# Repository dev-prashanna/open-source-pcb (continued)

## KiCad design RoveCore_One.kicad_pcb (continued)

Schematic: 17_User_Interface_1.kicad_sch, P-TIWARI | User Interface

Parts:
BZ1: PKLCS1212E4001-R1; Buzzer_Murata_PKLCS1212E; MPN PKLCS1212E4001-R1
C68: 100nF 16V; C_0603_1608Metric; MPN GRM188R71C104KA01D
D4, D6: GREEN; LED_0603_1608Metric; MPN LTST-C190KGKT
D5: RED; LED_0603_1608Metric; MPN LTST-C190KRKT
D7: BLUE; LED_0603_1608Metric; MPN LTST-C193TBKT-5A
D8: SS34; D_SMA; MPN SS34
Q6, Q7: AO3400A; SOT-23; MPN AO3400A
R62: 10k; R_0603_1608Metric; MPN RC0603FR-0710KL
R63, R64, R65, R66, R69: 1k; R_0603_1608Metric; MPN RC0603FR-071KL
R67, R70: 100; R_0603_1608Metric; MPN RC0603FR-07100RL
R68, R71: 100k; R_0603_1608Metric; MPN RC0603FR-07100KL
SW3: SW3; SW_Push_1P1T-SH_NO_CK_KMR2xxG; MPN KMR221GLFS

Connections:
+3V3: BZ1.1 (+), R62.1, R63.1, R64.1, R65.1, R66.1, R69.1; also elsewhere on the board
BAT5: D8.1 (K); also elsewhere on the board
BUZZ_GATE: Q6.1 (G), R67.2, R68.1
BUZZ_LOW: BZ1.2 (-), Q6.3 (D), R69.2
BUZZ_PWM: R67.1; also elsewhere on the board
EXP_B7: R70.1; also elsewhere on the board
GND: C68.2, D4.1 (K), Q6.2 (S), Q7.2 (S), R68.2, R71.2, SW3.2; also elsewhere on the board
LED_B: D7.2 (A), R66.2
LED_G: D6.2 (A), R65.2
LED_R: D5.2 (A), R64.2
LOAD_GATE: Q7.1 (G), R70.2, R71.1
LOAD_LOW: D8.2 (A), Q7.3 (D); also elsewhere on the board
POWER_LED: D4.2 (A), R63.2
RGB_B: D7.1 (K); also elsewhere on the board
RGB_G: D6.1 (K); also elsewhere on the board
RGB_R: D5.1 (K); also elsewhere on the board
USER_BTN: C68.1, R62.2, SW3.1; also elsewhere on the board

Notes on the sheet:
R/G/B discrete programmable LEDs on expander GPA5..7; use green for Wi-Fi status. Piezo buzzer via GPIO2 MOSFET and discharge resistor. User button active LOW on GPA4. GPB7 load output 5V/250mA max, diode-protected for small inductive loads. BAT5 accessory budget shared. CAN: external 3V3 transceiv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

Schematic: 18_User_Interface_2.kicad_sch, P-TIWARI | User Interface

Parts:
J23: LOAD 5V 0.25A; JST_GH_SM02B-GHS-TB_1x02-1MP_P1.25mm_Horizontal; MPN SM02B-GHS-TB(LF)(SN)

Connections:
BAT5: J23.1; also elsewhere on the board
LOAD_LOW: J23.2; also elsewhere on the board

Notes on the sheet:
R/G/B discrete programmable LEDs on expander GPA5..7; use green for Wi-Fi status. Piezo buzzer via GPIO2 MOSFET and discharge resistor. User button active LOW on GPA4. GPB7 load output 5V/250mA max, diode-protected for small inductive loads. BAT5 accessory budget shared. CAN: external 3V3 transceiv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

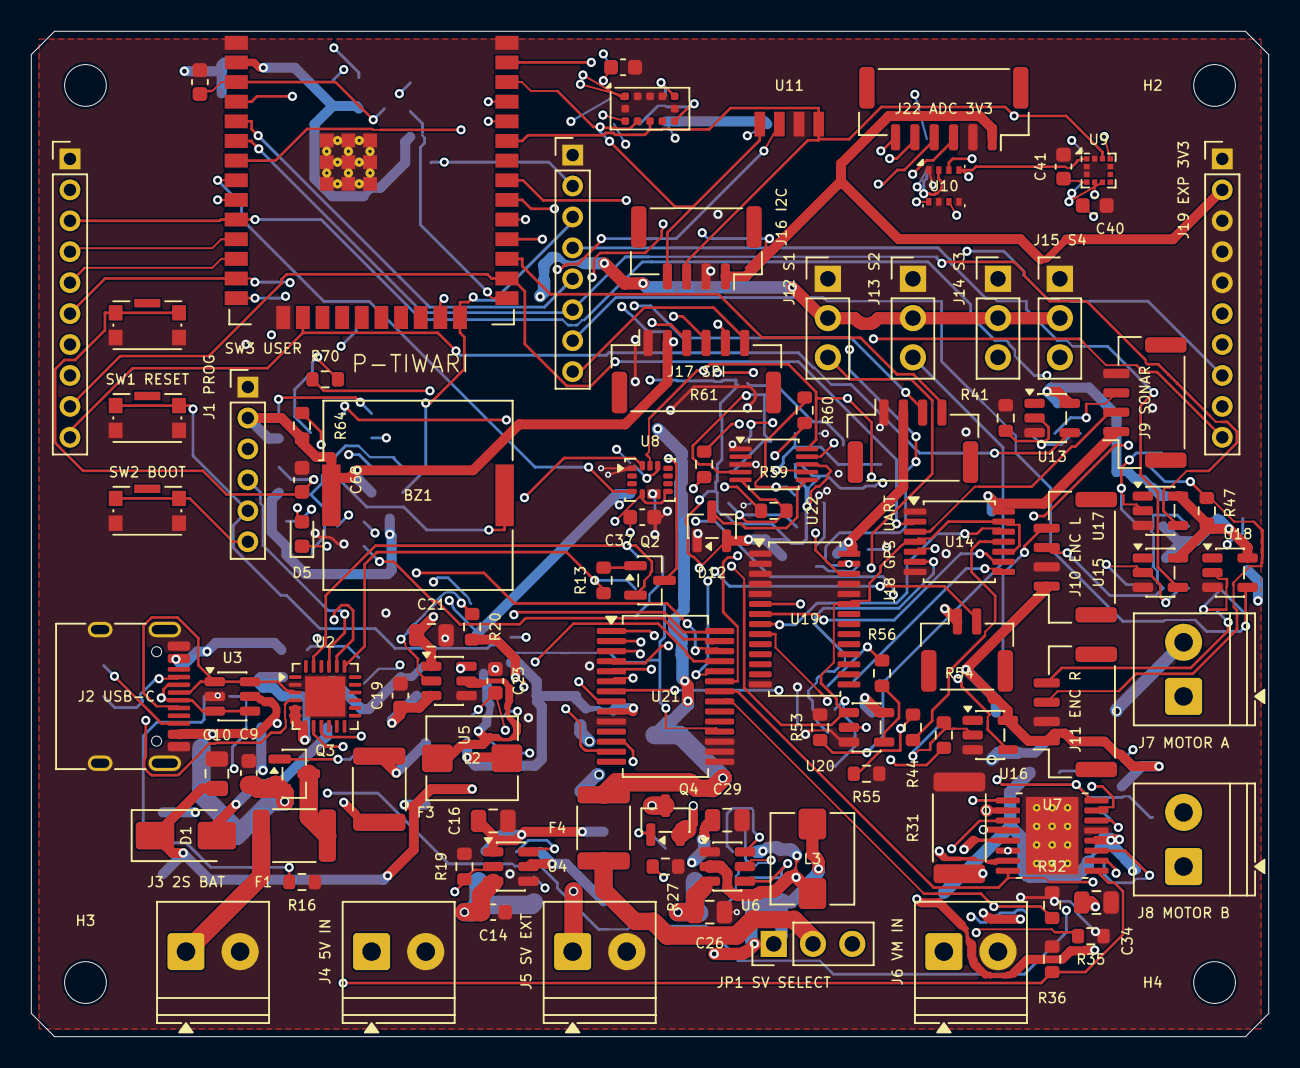
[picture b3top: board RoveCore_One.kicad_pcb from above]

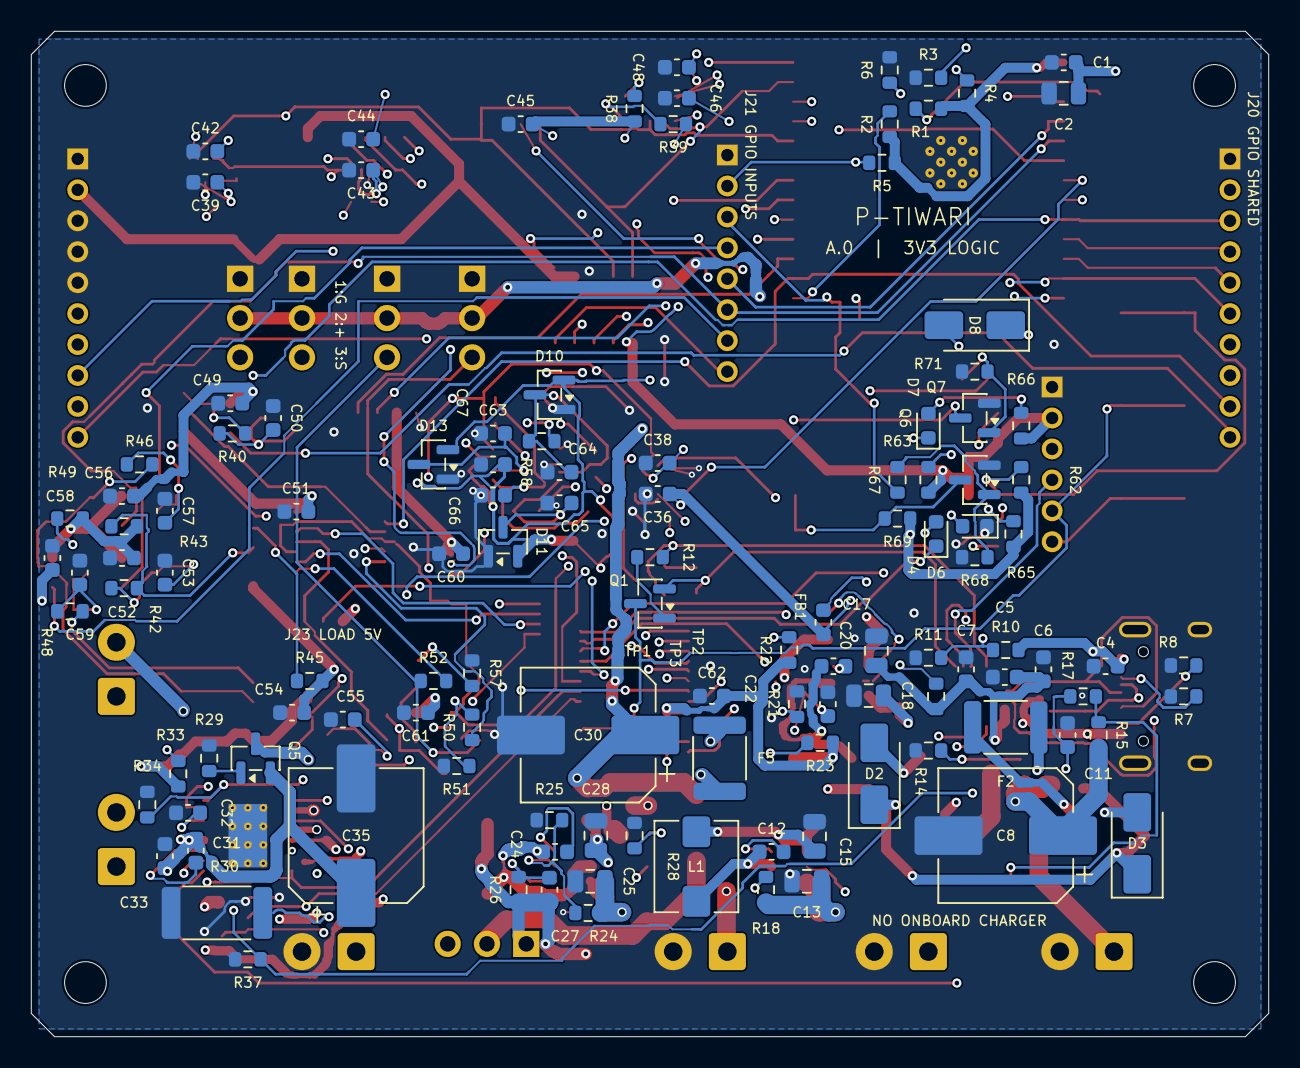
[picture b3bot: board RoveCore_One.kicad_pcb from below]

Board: 4 copper layers, 80.0 x 65.0 mm, 224 parts (122 on the bottom side), 135 nets.

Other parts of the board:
H1, H2, H3, H4: MountingHole_2.7mm_M2.5

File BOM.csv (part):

Reference,Value,MPN,Manufacturer,Footprint,Section,Datasheet
U1,ESP32-WROOM-32E-N8,ESP32-WROOM-32E-N8,Espressif,RoveCore:ESP32-WROOM-32E_Board,Controller,https://documentation.espressif.com/esp32-wroom-32e_esp32-wr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
C1,100nF 16V,GRM188R71C104KA01D,Murata,Capacitor_SMD:C_0603_1608Metric,Controller,
C2,22uF 10V,GRM21BR61A226ME44L,Murata,Capacitor_SMD:C_0805_2012Metric,Controller,
R1,10k,RC0603FR-0710KL,Yageo,Resistor_SMD:R_0603_1608Metric,Controller,
C3,1uF 16V,GRM188R61C105KA12D,Murata,Capacitor_SMD:C_0603_1608Metric,Controller,
R2,10k,RC0603FR-0710KL,Yageo,Resistor_SMD:R_0603_1608Metric,Controller,
R3,10k,RC0603FR-0710KL,Yageo,Resistor_SMD:R_0603_1608Metric,Controller,
R4,10k,RC0603FR-0710KL,Yageo,Resistor_SMD:R_0603_1608Metric,Controller,
R5,10k,RC0603FR-0710KL,Yageo,Resistor_SMD:R_0603_1608Metric,Controller,
R6,100k,RC0603FR-07100KL,Yageo,Resistor_SMD:R_0603_1608Metric,Controller,
SW1,SW1,KMR221GLFS,C&K,Button_Switch_SMD:SW_Push_1P1T-SH_NO_CK_KMR2xxG,Controller,
SW2,SW2,KMR221GLFS,C&K,Button_Switch_SMD:SW_Push_1P1T-SH_NO_CK_KMR2xxG,Controller,
J1,SERVICE 3V3,M22-2010605,Harwin,Connector_PinHeader_2.00mm:PinHeader_1x06_P2.00mm_Vertical,Controller,
J2,USB-C 5V DATA,TYPE-C-31-M-12,HRO,Connector_USB:USB_C_Receptacle_HRO_TYPE-C-31-M-12,USB Programming,
R7,5.1k,RC0603FR-075K1L,Yageo,Resistor_SMD:R_0603_1608Metric,USB Programming,
R8,5.1k,RC0603FR-075K1L,Yageo,Resistor_SMD:R_0603_1608Metric,USB Programming,
C4,1uF 16V,GRM188R61C105KA12D,Murata,Capacitor_SMD:C_0603_1608Metric,USB Programming,
U2,CP2102N-A02-GQFN24,CP2102N-A02-GQFN24,Silicon Labs,Package_DFN_QFN:QFN-24-1EP_4x4mm_P0.5mm_EP2.6x2.6mm,USB Programming,https://www.silabs.com/documents/public/data-sheets/cp2102n-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
C5,100nF 16V,GRM188R71C104KA01D,Murata,Capacitor_SMD:C_0603_1608Metric,USB Programming,
C6,100nF 16V,GRM188R71C104KA01D,Murata,Capacitor_SMD:C_0603_1608Metric,USB Programming,
C7,4.7uF 10V,GRM188R61A475KE15D,Murata,Capacitor_SMD:C_0603_1608Metric,USB Programming,
R9,1k,RC0603FR-071KL,Yageo,Resistor_SMD:R_0603_1608Metric,USB Programming,
R10,22.1k,RC0603FR-0722K1L,Yageo,Resistor_SMD:R_0603_1608Metric,USB Programming,
R11,47.5k,RC0603FR-0747K5L,Yageo,Resistor_SMD:R_0603_1608Metric,USB Programming,
U3,USBLC6-2SC6,USBLC6-2SC6,STMicroelectronics,Package_TO_SOT_SMD:SOT-23-6,USB Programming,
Q1,MMBT3904,MMBT3904,onsemi,Package_TO_SOT_SMD:SOT-23,USB Programming,
R12,10k,RC0603FR-0710KL,Yageo,Resistor_SMD:R_0603_1608Metric,USB Programming,
Q2,MMBT3904,MMBT3904,onsemi,Package_TO_SOT_SMD:SOT-23,USB Programming,
R13,10k,RC0603FR-0710KL,Yageo,Resistor_SMD:R_0603_1608Metric,USB Programming,
J3,2S BAT 6.4-8.4V,1984617,Phoenix Contact,"TerminalBlock_Phoenix:TerminalBlock_Phoenix_PT-1,5-2-3.5-H_1x02_P3.50mm_Horizontal",Power Inputs,
F1,2A hold,1812L200/16DR,Littelfuse,Fuse:Fuse_1812_4532Metric,Power Inputs,
Q3,AO3401A,AO3401A,Alpha & Omega Semiconductor,Package_TO_SOT_SMD:SOT-23,Power Inputs,https://www.aosmd.com/sites/default/files/res/datasheets/AO3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
R14,100k,RC0603FR-07100KL,Yageo,Resistor_SMD:R_0603_1608Metric,Power Inputs,
C8,470uF 16V,EEE-FK1C471P,Panasonic,Capacitor_SMD:CP_Elec_8x10.5,Power Inputs,
C9,100nF 16V,GRM188R71C104KA01D,Murata,Capacitor_SMD:C_0603_1608Metric,Power Inputs,
J4,EXT 5V LOGIC,1984617,Phoenix Contact,"TerminalBlock_Phoenix:TerminalBlock_Phoenix_PT-1,5-2-3.5-H_1x02_P3.50mm_Horizontal",Power Inputs,
F2,1.1A hold,1812L110/16DR,Littelfuse,Fuse:Fuse_1812_4532Metric,Power Inputs,
F3,0.5A hold,1812L050/24DR,Littelfuse,Fuse:Fuse_1812_4532Metric,Power Inputs,
D1,SS34,SS34,Diodes Inc.,Diode_SMD:D_SMA,Power Inputs,
D2,SS34,SS34,Diodes Inc.,Diode_SMD:D_SMA,Power Inputs,
D3,SS34,SS34,Diodes Inc.,Diode_SMD:D_SMA,Power Inputs,
C10,22uF 10V,GRM21BR61A226ME44L,Murata,Capacitor_SMD:C_0805_2012Metric,Power Inputs,
R15,100k,RC0603FR-07100KL,Yageo,Resistor_SMD:R_0603_1608Metric,Power Inputs,
R16,33k,RC0603FR-0733KL,Yageo,Resistor_SMD:R_0603_1608Metric,Power Inputs,
R17,1k,RC0603FR-071KL,Yageo,Resistor_SMD:R_0603_1608Metric,Power Inputs,
C11,100nF 16V,GRM188R71C104KA01D,Murata,Capacitor_SMD:C_0603_1608Metric,Power Inputs,
U4,AP63205WU-7,AP63205WU-7,Diodes Inc.,Package_TO_SOT_SMD:TSOT-23-6,Logic Regulators,https://www.diodes.com/datasheet/download/AP63200-AP63201-AP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
R18,100k,RC0603FR-07100KL,Yageo,Resistor_SMD:R_0603_1608Metric,Logic Regulators,
R19,27.4k,RC0603FR-0727K4L,Yageo,Resistor_SMD:R_0603_1608Metric,Logic Regulators,
C12,100nF 16V,GRM188R71C104KA01D,Murata,Capacitor_SMD:C_0603_1608Metric,Logic Regulators,
C13,10uF 16V,GRM21BR61C106KE15L,Murata,Capacitor_SMD:C_0805_2012Metric,Logic Regulators,
C14,100nF 16V,GRM188R71C104KA01D,Murata,Capacitor_SMD:C_0603_1608Metric,Logic Regulators,
L1,4.7uH,SRP5030T-4R7M,Bourns,Inductor_SMD:L_Bourns_SRP5030T,Logic Regulators,
C15,22uF 10V,GRM21BR61A226ME44L,Murata,Capacitor_SMD:C_0805_2012Metric,Logic Regulators,
C16,22uF 10V,GRM21BR61A226ME44L,Murata,Capacitor_SMD:C_0805_2012Metric,Logic Regulators,
U5,AP63203WU-7,AP63203WU-7,Diodes Inc.,Package_TO_SOT_SMD:TSOT-23-6,Logic Regulators,https://www.diodes.com/datasheet/download/AP63200-AP63201-AP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
R20,100k,RC0603FR-07100KL,Yageo,Resistor_SMD:R_0603_1608Metric,Logic Regulators,
R21,100k,RC0603FR-07100KL,Yageo,Resistor_SMD:R_0603_1608Metric,Logic Regulators,
C17,100nF 16V,GRM188R71C104KA01D,Murata,Capacitor_SMD:C_0603_1608Metric,Logic Regulators,
C18,10uF 16V,GRM21BR61C106KE15L,Murata,Capacitor_SMD:C_0805_2012Metric,Logic Regulators,
C19,100nF 16V,GRM188R71C104KA01D,Murata,Capacitor_SMD:C_0603_1608Metric,Logic Regulators,
L2,4.7uH,SRP5030T-4R7M,Bourns,Inductor_SMD:L_Bourns_SRP5030T,Logic Regulators,
C20,22uF 10V,GRM21BR61A226ME44L,Murata,Capacitor_SMD:C_0805_2012Metric,Logic Regulators,
C21,22uF 10V,GRM21BR61A226ME44L,Murata,Capacitor_SMD:C_0805_2012Metric,Logic Regulators,
FB1,600R @100MHz,BLM18AG601SN1D,Murata,Inductor_SMD:L_0603_1608Metric,Logic Regulators,
C22,4.7uF 10V,GRM188R61A475KE15D,Murata,Capacitor_SMD:C_0603_1608Metric,Logic Regulators,
C23,100nF 16V,GRM188R71C104KA01D,Murata,Capacitor_SMD:C_0603_1608Metric,Logic Regulators,
R22,2.2k,RC0603FR-072K2L,Yageo,Resistor_SMD:R_0603_1608Metric,Logic Regulators,
R23,2.2k,RC0603FR-072K2L,Yageo,Resistor_SMD:R_0603_1608Metric,Logic Regulators,
U6,TPS54302DDCR,TPS54302DDCR,Texas Instruments,Package_TO_SOT_SMD:SOT-23-6,Servo Power,https://www.ti.com/lit/ds/symlink/tps54302.pdf
R24,100k,RC0603FR-07100KL,Yageo,Resistor_SMD:R_0603_1608Metric,Servo Power,
R25,27.4k,RC0603FR-0727K4L,Yageo,Resistor_SMD:R_0603_1608Metric,Servo Power,
C24,100nF 16V,GRM188R71C104KA01D,Murata,Capacitor_SMD:C_0603_1608Metric,Servo Power,
C25,10uF 16V,GRM21BR61C106KE15L,Murata,Capacitor_SMD:C_0805_2012Metric,Servo Power,
C26,10uF 16V,GRM21BR61C106KE15L,Murata,Capacitor_SMD:C_0805_2012Metric,Servo Power,
L3,10uH,SRP5030T-100M,Bourns,Inductor_SMD:L_Bourns_SRP5030T,Servo Power,
R26,100k,RC0603FR-07100KL,Yageo,Resistor_SMD:R_0603_1608Metric,Servo Power,
R27,13.3k,RC0603FR-0713K3L,Yageo,Resistor_SMD:R_0603_1608Metric,Servo Power,
C27,75pF 50V,GRM1885C1H750JA01D,Murata,Capacitor_SMD:C_0603_1608Metric,Servo Power,
C28,22uF 10V,GRM21BR61A226ME44L,Murata,Capacitor_SMD:C_0805_2012Metric,Servo Power,
C29,22uF 10V,GRM21BR61A226ME44L,Murata,Capacitor_SMD:C_0805_2012Metric,Servo Power,
J5,SERVO EXT 5-6V,1984617,Phoenix Contact,"TerminalBlock_Phoenix:TerminalBlock_Phoenix_PT-1,5-2-3.5-H_1x02_P3.50mm_Horizontal",Servo Power,
Q4,AO3401A,AO3401A,Alpha & Omega Semiconductor,Package_TO_SOT_SMD:SOT-23,Servo Power,https://www.aosmd.com/sites/default/files/res/datasheets/AO3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
R28,100k,RC0603FR-07100KL,Yageo,Resistor_SMD:R_0603_1608Metric,Servo Power,
JP1,SERVO SELECT 1-2 BAT / 2-3 EXT,61300311121,Wurth Elektronik,Connector_PinHeader_2.54mm:PinHeader_1x03_P2.54mm_Vertical,Servo Power,
F4,2A hold,1812L200/16DR,Littelfuse,Fuse:Fuse_1812_4532Metric,Servo Power,
C30,470uF 16V,EEE-FK1C471P,Panasonic,Capacitor_SMD:CP_Elec_8x10.5,Servo Power,
J6,VM 3-8.4V,1984617,Phoenix Contact,"TerminalBlock_Phoenix:TerminalBlock_Phoenix_PT-1,5-2-3.5-H_1x02_P3.50mm_Horizontal",Motor Driver,
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
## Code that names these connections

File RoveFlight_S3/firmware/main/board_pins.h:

// Generated from verified GPIO_Allocation.csv. RF-S3-A0 / N8R2 only.
#pragma once
#define PIN_BOOT 0
#define PIN_CURRENT_ADC 1
#define PIN_BAT_ADC 2
#define PIN_PWM_M1 4
#define PIN_PWM_M2 5
#define PIN_PWM_M3 6
#define PIN_PWM_M4 7
#define PIN_I2C_SDA 8
#define PIN_IMU_INT 9
#define PIN_IMU_CS 10
#define PIN_SPI_MOSI 11
#define PIN_SPI_SCK 12
#define PIN_SPI_MISO 13
#define PIN_BARO_CS 14
#define PIN_IR_RX 15
#define PIN_TOF_INT 16
#define PIN_TOF_XSHUT 17
#define PIN_I2C_SCL 18
#define PIN_USB_DM 19
#define PIN_USB_DP 20
#define PIN_STATUS_LED 21
#define PIN_ARM_CLK 38
#define PIN_WD_HEARTBEAT 39
#define PIN_KILL_OD 40
#define PIN_RC_RX 41
#define PIN_RC_TX 42
#define PIN_DEBUG_TX 43
#define PIN_DEBUG_RX 44
#define PIN_FLOW_CS 47
#define PIN_FLOW_INT 48

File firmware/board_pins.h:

// P-TIWARI A.0; pin contract only, not validated application firmware.
#pragma once
namespace p_tiwari {
constexpr int PIN_BOOT = 0;
constexpr int PIN_U0_TX = 1;
constexpr int PIN_BUZZ_PWM = 2;
constexpr int PIN_U0_RX = 3;
constexpr int PIN_US_TRIG = 4;
constexpr int PIN_SPI_CS = 5;
constexpr int PIN_STRAP12 = 12;
constexpr int PIN_US_ECHO = 13;
constexpr int PIN_M_B2 = 14;
constexpr int PIN_SERVO_OE = 15;
constexpr int PIN_UART_RX = 16;
constexpr int PIN_UART_TX = 17;
constexpr int PIN_SPI_SCK = 18;
constexpr int PIN_SPI_MISO = 19;
constexpr int PIN_I2C_SDA = 21;
constexpr int PIN_I2C_SCL = 22;
constexpr int PIN_SPI_MOSI = 23;
constexpr int PIN_M_A1 = 25;
constexpr int PIN_M_A2 = 26;
constexpr int PIN_M_B1 = 27;
constexpr int PIN_IMU_INT = 32;
constexpr int PIN_BAT_ADC = 33;
constexpr int PIN_ENC_RA = 34;
constexpr int PIN_ENC_RB = 35;
constexpr int PIN_ENC_LA = 36;
constexpr int PIN_ENC_LB = 39;
constexpr unsigned IMU_ADDR=0x6A, MAG_ADDR=0x1C, BME_ADDR=0x76, ALS_ADDR=0x10;
constexpr unsigned TOF_ADDR=0x29, PWM_ADDR=0x40, EXP_ADDR=0x20, ADC_ADDR=0x48;
}

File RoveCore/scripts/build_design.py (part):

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
d.section='Encoder Interfaces'
for idx,xy,labels,raws in [(0,(72,33),['ENC_LA','ENC_LB'],['ENC_LA_RAW','ENC_LB_RAW']),(1,(72,38),['ENC_RA','ENC_RB'],['ENC_RA_RAW','ENC_RB_RAW'])]:
 d.conn('J'+str(10+idx),['+3V3','GND',*raws],'ENC '+('LEFT' if idx==0 else 'RIGHT'),xy,'gh',90)
 for j,(net,raw) in enumerate(zip(labels,raws)):
  ref='U'+str(15+idx*2+j)
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for ref,net,xy in [('TP1','EXP_B0',(40.2806,39.0703)),('TP2','EXP_B1',(39.4113,39.4811)),('TP3','EXP_B2',(39.377,40.2551))]:
 d.add('Connector','TestPoint',net,{'1':net},'RoveCore:ServicePad_0.5mm',xy,ref=ref,mpn='PCB copper feature',mfr='PCB fabricator',side='B')
# Shared test/header access to every practical controller pin; GPIO12 is reserved.
d.conn('J20',['GND','+3V3','M_A1','M_A2','M_B1','M_B2','IMU_INT','BAT_ADC','US_TRIG','US_ECHO'],'ESP GPIO SHARED',(6,7),'header')
d.conn('J21',['GND','SERVO_OE','BUZZ_PWM','ENC_LA','ENC_LB','ENC_RA','ENC_RB','SPI_CS'],'ESP GPIO INPUTS',(35,8),'header')
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
d.section='Analog Expansion'
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
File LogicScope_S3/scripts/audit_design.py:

"""Independent manifest/XML/PCB pin checks and ground-return geometry audit."""
from route_utils import *
import xml.etree.ElementTree as ET
from collections import defaultdict
from shapely.ops import unary_union
parts=json.loads((ROOT/'design.json').read_text());manifest={(c['ref'],pin):net for c in parts for pin,net in c['nets'].items()};xml=ET.parse(ROOT/'reports/LogicScope_S3.xml').getroot();actual={}
for net in xml.find('nets'):
 for q in net.findall('node'):actual[(q.attrib['ref'],q.attrib['pin'])]=net.attrib['name'].lstrip('/')
errors=[]
for (ref,num),net in manifest.items():
 pads=[q for q in fps[ref].Pads() if q.GetNumber()==num]
 if not pads:errors.append([ref,num,'missing pad'])
 for q in pads:
  if net is None:
   if q.GetNetname() and not q.GetNetname().startswith('unconnected-'):errors.append([ref,num,'unexpected connected NC',q.GetNetname()])
  elif actual.get((ref,num))!=net or q.GetNetname()!=net:errors.append([ref,num,net,actual.get((ref,num)),q.GetNetname()])
for key,net in actual.items():
 if not key[0].startswith('#') and key not in manifest and not net.startswith('unconnected-'):errors.append(['unexpected pin',key,net])
def nn(ref,num):return actual.get((ref,str(num)))
checks={
 'manifest_schematic_and_pcb_match':not errors,
 'eight_parallel_bits':all(nn('U1',4+i)==nn('U2',18-i)==f'D{i}' for i in range(8)),
 'input_protection_each_channel':all(nn('R'+str(10+i),1)==f'CH{i}' and nn('R'+str(10+i),2)==nn('U2',2+i)==f'IN{i}' for i in range(8)),
 'pulldowns_each_input':all(nn('R'+str(20+i),1)==f'IN{i}' and nn('R'+str(20+i),2)=='GND' for i in range(8)),
 'buffer_direction_and_supply':nn('U2',1)==nn('U2',20)=='+3V3' and nn('U2',10)=='GND' and nn('U2',19)=='BUF_OE_N',
 'usb_native_gpio19_20':nn('U1',13)=='USB_DM' and nn('U1',14)=='USB_DP',
 'usb_dual_data_pads':nn('J3','A6')==nn('J3','B6')=='USB_DP_CONN' and nn('J3','A7')==nn('J3','B7')=='USB_DM_CONN',
 'usb_cc_separate':nn('J3','A5')==nn('R30',1)=='USB_CC1' and nn('J3','B5')==nn('R31',1)=='USB_CC2' and nn('R30',2)==nn('R31',2)=='GND',
 'buck_pin_map':all(nn('U3',pin)==net for pin,net in [(1,'+3V3'),(2,'VUSB'),(3,'VUSB'),(4,'GND'),(5,'SW'),(6,'BST')]),
 'hardware_clock_loopback':nn('U1',20)==nn('R4',1)=='SAMPLE_CLK' and nn('R4',2)==nn('U1',19)=='CAM_PCLK',
 'no_external_5V_direct_to_mcu':not any(q.GetNetname() in {'USB_5V','VUSB'} or q.GetNetname().startswith('CH') for q in fps['U1'].Pads()),
 'two_copper_layers':b.GetCopperLayerCount()==2,
 'optional_esd_dnp':all(bool(fps[ref].GetAttributes()&p.FP_DNP) for ref in ['U5','U6']),
 'etched_and_silk_tiwari':all(any(isinstance(q,p.PCB_TEXT) and q.GetText()=='TIWARI' and q.GetLayer()==layer for q in b.GetDrawings()) for layer in [p.F_Cu,p.F_SilkS]),
}
for ref,nets in [('J1',['CH0','GND','CH1','GND','CH2','GND','CH3','GND','CH4','GND']),('J2',['CH5','GND','CH6','GND','CH7','GND','VREF_3V3','GND',None,None])]:
 checks[ref+'_pinout']=all(nn(ref,i+1)==net if net else nn(ref,i+1).startswith('unconnected-') for i,net in enumerate(nets))
connectivity={'checks':checks,'errors':errors,'electrical_parts':len(parts),'all_passed':all(checks.values())}
(ROOT/'reports/Connectivity_Audit.json').write_text(json.dumps(connectivity,indent=2)+'\n')

def filled(z):
 ps=z.GetFilledPolysList(z.GetLayer())
 def ring(r):return [(p.ToMM(r.CPoint(k).x),p.ToMM(r.CPoint(k).y)) for k in range(r.PointCount())]
 return [Polygon(ring(ps.COutline(i)),[ring(ps.CHole(i,j)) for j in range(ps.HoleCount(i))]).buffer(0) for i in range(ps.OutlineCount())]
rear_zones=[z for z in b.Zones() if not z.GetIsRuleArea() and z.GetLayer()==p.B_Cu and z.GetNetname()=='GND']
rear_polys=[g for z in rear_zones for g in filled(z)];rear=unary_union(rear_polys)
netstats=defaultdict(lambda:{'length_mm':0.,'rear_length_mm':0.,'vias':0,'widths_mm':set(),'layers':set()});critical_errors=[];plane_gaps=[];via_pad=[]
for tr in b.GetTracks():
 net=tr.GetNetname();e=netstats[net]
 if isinstance(tr,p.PCB_VIA):
  e['vias']+=1;hole=Point(*xy(tr)).buffer(p.ToMM(tr.GetDrill())/2)
  if any(hole.intersects(g) for l in layers for g in smd[l]):via_pad.append({'net':net,'xy':xy(tr)})
  continue
 a,z=tr.GetStart(),tr.GetEnd();path=LineString([(p.ToMM(a.x),p.ToMM(a.y)),(p.ToMM(z.x),p.ToMM(z.y))]);length=p.ToMM(tr.GetLength());e['length_mm']+=length;e['widths_mm'].add(round(p.ToMM(tr.GetWidth()),4));e['layers'].add(b.GetLayerName(tr.GetLayer()))
 if tr.GetLayer()==p.B_Cu:e['rear_length_mm']+=length
 if net in {f'D{i}' for i in range(8)} or net.startswith('USB_D'):
  if tr.GetLayer()!=p.F_Cu:critical_errors.append(net)
  if not rear.buffer(.01).covers(path):plane_gaps.append({'net':net,'length_missing_mm':path.difference(rear.buffer(.01)).length})
for e in netstats.values():
 for key in ['length_mm','rear_length_mm']:e[key]=round(e[key],4)
 for key in ['layers','widths_mm']:e[key]=sorted(e[key])
critical_vias={n:e['vias'] for n,e in netstats.items() if (n.startswith('USB_D') or n in {f'D{i}' for i in range(8)}) and e['vias']}
antenna=[]
for fp in b.GetFootprints():
 for zone in fp.Zones():
  if not zone.GetIsRuleArea():continue
  ps=zone.Outline()
  for i in range(ps.OutlineCount()):
   r=ps.COutline(i);g=Polygon([(p.ToMM(r.CPoint(k).x),p.ToMM(r.CPoint(k).y)) for k in range(r.PointCount())])
   for l in layers:
    if any(g.intersection(s).area>1e-5 for s,n in zip(geoms[l],owners[l]) if n!='__KEEP_OUT'):antenna.append('copper overlap')
   if g.intersection(rear).area>1e-5:antenna.append('rear fill overlap')
physical={'copper_layers':b.GetCopperLayerCount(),'board_mm':[55,40],'nominal_thickness_mm':p.ToMM(b.GetDesignSettings().GetBoardThickness()),'footprints':len(fps),'rear_ground_polygons':len(rear_polys),'rear_ground_area_mm2':round(rear.area,3),'rear_coverage_of_2200mm2_percent':round(100*rear.area/2200,2),'critical_routes_on_wrong_layer':critical_errors,'critical_vias':critical_vias,'critical_centerline_reference_gaps':plane_gaps,'antenna_copper_errors':antenna,'board_via_drills_in_smd_lands':via_pad,'nets':dict(netstats),'performance_validation':'UNMEASURED; finite capture target 1 MS/s, no released continuous rate'}
physical['all_passed']=len(rear_polys)==1 and not any([critical_errors,critical_vias,plane_gaps,antenna,via_pad])
(ROOT/'reports/Physical_Audit.json').write_text(json.dumps(physical,indent=2)+'\n')
with (ROOT/'Placement.csv').open('w') as f:
 w=csv.writer(f);w.writerow(['Reference','Value','X_mm','Y_mm','Rotation_deg','Side','DNP'])
 for ref,fp in sorted(fps.items()):w.writerow([ref,fp.GetValue(),*xy(fp),fp.GetOrientationDegrees(),'F' if fp.GetLayer()==p.F_Cu else 'B','YES' if fp.GetAttributes()&p.FP_DNP else 'NO'])
print('Connectivity checks',checks,'errors',errors)
print('Physical audit:',{k:v for k,v in physical.items() if k!='nets'})
if not connectivity['all_passed'] or not physical['all_passed']:raise SystemExit(1)
